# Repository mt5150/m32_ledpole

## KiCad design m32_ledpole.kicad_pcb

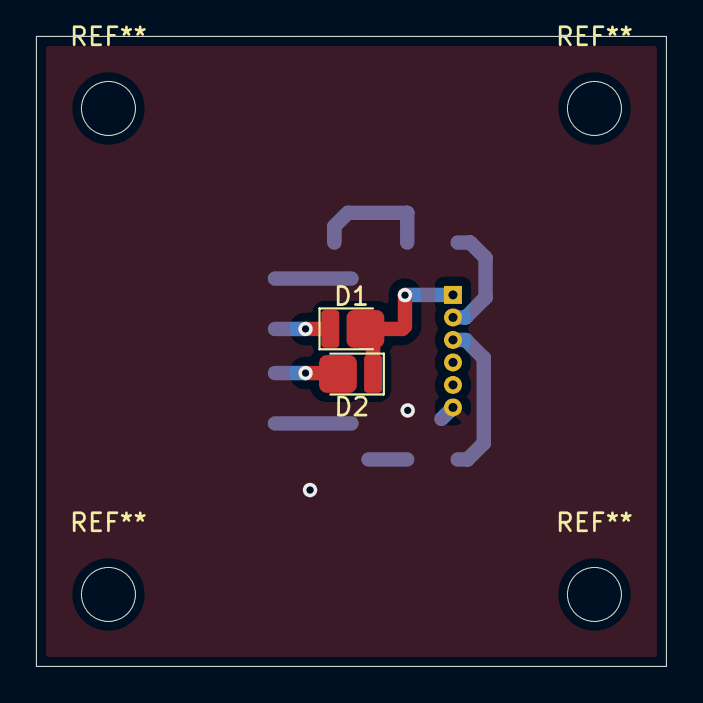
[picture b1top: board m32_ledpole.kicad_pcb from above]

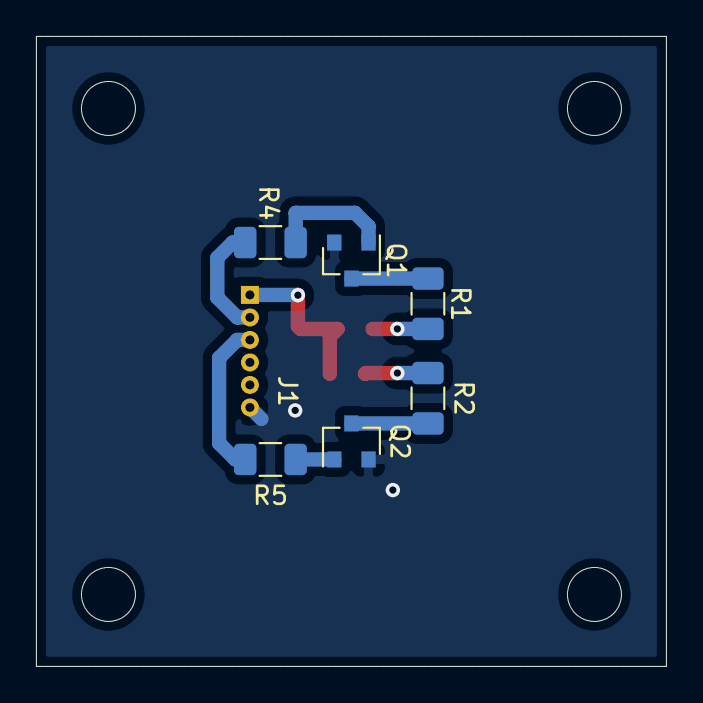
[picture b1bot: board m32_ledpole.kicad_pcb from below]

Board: 2 copper layers, 35.0 x 35.0 mm, 9 parts (7 on the bottom side), 10 nets.

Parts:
D1: LED; LED_2835Metric_RI35TS
D2: LED; LED_2835Metric_RI35TS_reversed
J1: Conn_01x06_Male; JOINT_TECH_A1250WV-6P_rev
Q1, Q2: Q_NPN_BEC; SOT-23
R1: 68; R_1206_3216Metric
R2: 100; R_1206_3216Metric
R4, R5: 10k; R_1206_3216Metric

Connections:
+5V: D1.2, D2.2, J1.1
/GREEN: J1.3, R5.1
/RED: J1.2, R4.1
GND: J1.6, Q1.2, Q2.2
unnamed: D1.1, R1.2
unnamed: D2.1, R2.2
unnamed: Q1.1, R4.2
unnamed: Q1.3, R1.1
unnamed: Q2.1, R5.2
unnamed: Q2.3, R2.1

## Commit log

2023-06-05 init
2023-06-05 tiding
